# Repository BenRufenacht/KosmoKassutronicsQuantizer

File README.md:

# KosmoKassutronicsQuantizer
 Kassutronics Quantizer in Kosmo Format

[Build Docs from Kassutronics](https://github.com/kassu/kassutronics/blob/master/documentation/Quantizer/Quantizer_Build_Docs_1.1A.pdf)

Status:   
Oct 2023 Updated Back PCB to fix potential shorting issue with the Trigger input jacks and fixed a connection error that prevented free running mode from working. These updates to the back pcb are untested.

License:  
[CC-BY-SA](https://creativecommons.org/licenses/by-sa/3.0/)

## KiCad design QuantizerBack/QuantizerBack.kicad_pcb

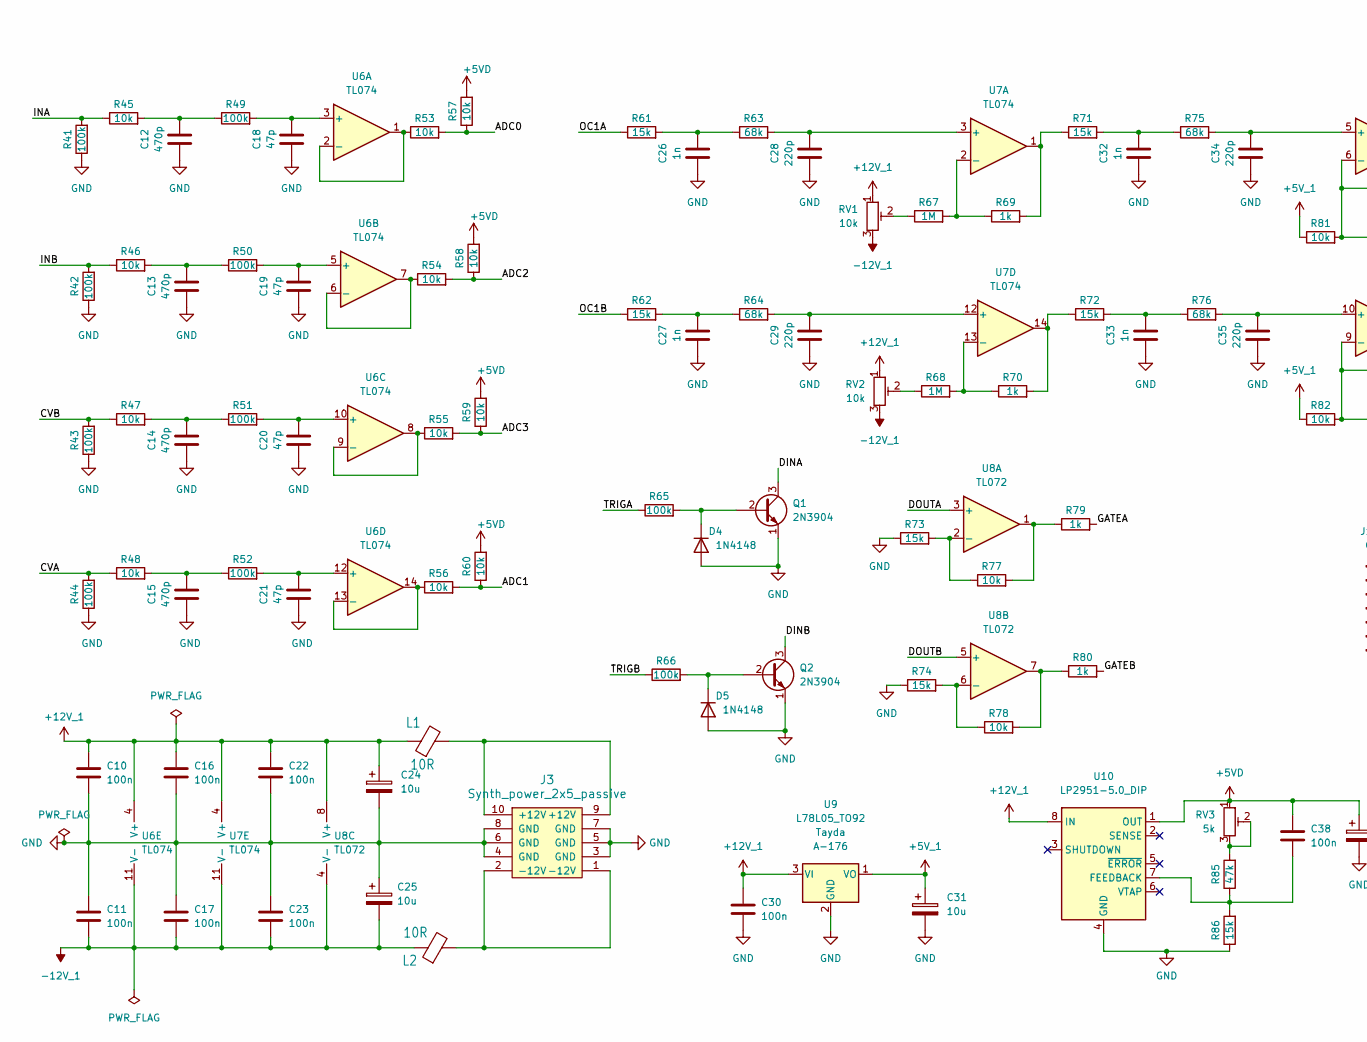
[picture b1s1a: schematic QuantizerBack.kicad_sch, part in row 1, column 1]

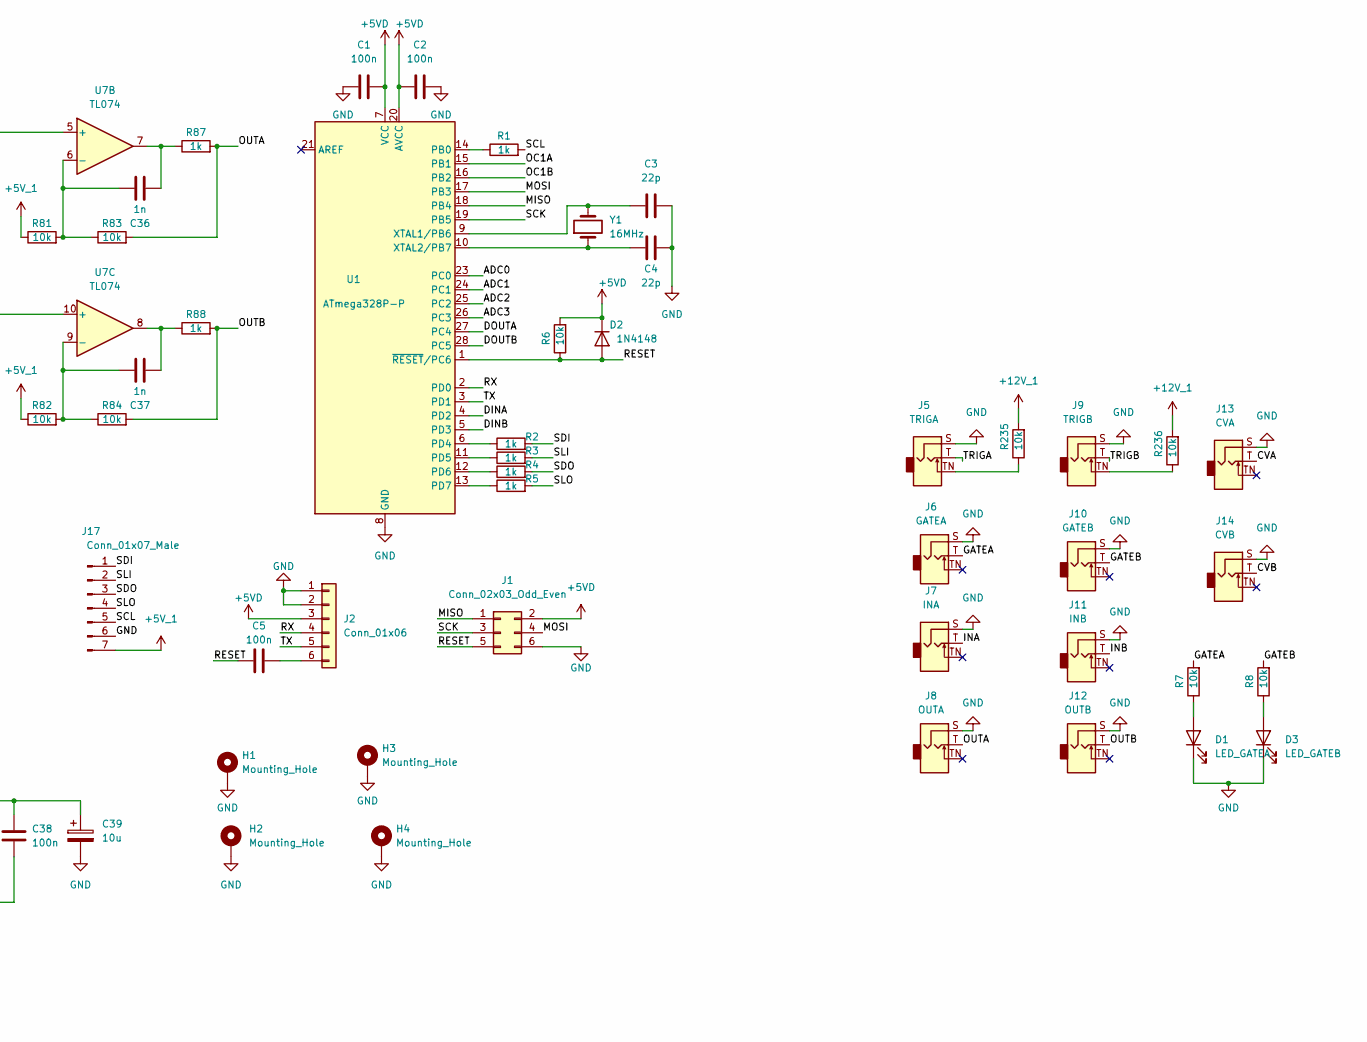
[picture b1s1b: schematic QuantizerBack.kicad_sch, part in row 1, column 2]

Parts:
C1, C2, C5, C10, C11, C16, C17, C22, C23, C30, C38: 100n; C_Rect_L7.2mm_W2.5mm_P5.00mm_FKS2_FKP2_MKS2_MKP2
C3, C4: 22p; C_Rect_L7.2mm_W2.5mm_P5.00mm_FKS2_FKP2_MKS2_MKP2
C12, C13, C14, C15: 470p; C_Rect_L7.2mm_W2.5mm_P5.00mm_FKS2_FKP2_MKS2_MKP2
C18, C19, C20, C21: 47p; C_Rect_L7.2mm_W2.5mm_P5.00mm_FKS2_FKP2_MKS2_MKP2
C24, C25, C31, C39: 10u; CP_Radial_D6.3mm_P2.50mm
C26, C27, C32, C33, C36, C37: 1n; C_Rect_L7.2mm_W2.5mm_P5.00mm_FKS2_FKP2_MKS2_MKP2
C28, C29, C34, C35: 220p; C_Rect_L7.2mm_W2.5mm_P5.00mm_FKS2_FKP2_MKS2_MKP2
D1: LED_GATEA; LED_D5.0mm
D2, D4, D5: 1N4148; D_DO-35_SOD27_P7.62mm_Horizontal
D3: LED_GATEB; LED_D5.0mm
H1, H2, H3, H4: Mounting_Hole; Kosmo_Panel_Mounting_Hole
J1: Conn_02x03_Odd_Even; PinHeader_2x03_P2.54mm_Vertical
J2: Conn_01x06; PinHeader_1x06_P2.54mm_Vertical
J3: Synth_power_2x5_passive; Power_Header
J5: TRIGA; Jack_6.35mm_PJ_629HAN
J6: GATEA; Jack_6.35mm_PJ_629HAN
J7: INA; Jack_6.35mm_PJ_629HAN
J8: OUTA; Jack_6.35mm_PJ_629HAN
J9: TRIGB; Jack_6.35mm_PJ_629HAN
J10: GATEB; Jack_6.35mm_PJ_629HAN
J11: INB; Jack_6.35mm_PJ_629HAN
J12: OUTB; Jack_6.35mm_PJ_629HAN
J13: CVA; Jack_6.35mm_PJ_629HAN
J14: CVB; Jack_6.35mm_PJ_629HAN
J17: Conn_01x07_Male; PinHeader_1x07_P2.54mm_Vertical
L1, L2: 10R; L_Axial_L5.0mm_D3.6mm_P10.00mm_Horizontal_Murata_BL01RN1A2A2
Q1, Q2: 2N3904; TO-92_Inline_Wide
R1, R2, R3, R4, R5, R69, R70, R79, R80, R87, R88: 1k; R_Axial_DIN0207_L6.3mm_D2.5mm_P10.16mm_Horizontal
R6, R7, R8, R45, R46, R47, R48, R53, R54, R55, R56, R57, R58, R59, R60, R77, R78, R81, R82, R83, R84, R235, R236: 10k; R_Axial_DIN0207_L6.3mm_D2.5mm_P10.16mm_Horizontal
R41, R42, R43, R44, R49, R50, R51, R52, R65, R66: 100k; R_Axial_DIN0207_L6.3mm_D2.5mm_P10.16mm_Horizontal
R61, R62, R71, R72, R73, R74, R86: 15k; R_Axial_DIN0207_L6.3mm_D2.5mm_P10.16mm_Horizontal
R63, R64, R75, R76: 68k; R_Axial_DIN0207_L6.3mm_D2.5mm_P10.16mm_Horizontal
R67, R68: 1M; R_Axial_DIN0207_L6.3mm_D2.5mm_P10.16mm_Horizontal
R85: 47k; R_Axial_DIN0207_L6.3mm_D2.5mm_P10.16mm_Horizontal
RV1, RV2: 10k; Potentiometer_Bourns_3296W_Vertical_standard
RV3: 5k; Potentiometer_Bourns_3296W_Vertical_standard
U1: ATmega328P-P; DIP-28_W7.62mm
U6, U7: TL074; DIP-14_W7.62mm_Socket_LongPads
U8: TL072; DIP-8_W7.62mm_Socket_LongPads
U9: L78L05_TO92; TO-92_Inline
U10: LP2951-5.0_DIP; DIP-8_W7.62mm
Y1: 16MHz; Crystal_HC49-U_Vertical

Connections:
+5VD: C1.2, C2.1, C38.1, C39.1, D2.1 (K), J1.2, J2.3, R6.2, R57.2, R58.2, R59.2, R60.2, RV3.1, U1.7 (VCC), U1.20 (AVCC), U10.1 (OUT)
+5V_1: C31.1, J17.7, R81.1, R82.1, U9.1 (VO)
+12V_1: C10.1, C16.1, C22.1, C24.1, C30.1, L1.1, R235.2, R236.2, RV1.1, RV2.1, U6.4 (V+), U7.4 (V+), U8.8 (V+), U9.3 (VI), U10.8 (IN)
-12V_1: C11.1, C17.1, C23.1, C25.2, L2.1, RV1.3, RV2.3, U6.11 (V-), U7.11 (V-), U8.4 (V-)
/ADC0: R53.2, R57.1, U1.23 (PC0)
/ADC1: R56.2, R60.1, U1.24 (PC1)
/ADC2: R54.2, R58.1, U1.25 (PC2)
/ADC3: R55.2, R59.1, U1.26 (PC3)
/CVA: J13.T, R44.2, R48.1
/CVB: J14.T, R43.2, R47.1
/DINA: Q1.3 (C), U1.4 (PD2)
/DINB: Q2.3 (C), U1.5 (PD3)
/DOUTA: U1.27 (PC4), U8.3 (+)
/DOUTB: U1.28 (PC5), U8.5 (+)
/GATEA: J6.T, R7.2, R79.2
/GATEB: J10.T, R8.2, R80.2
/INA: J7.T, R41.2, R45.1
/INB: J11.T, R42.2, R46.1
/MISO: J1.1, U1.18 (PB4)
/MOSI: J1.4, U1.17 (PB3)
/OC1A: R61.1, U1.15 (PB1)
/OC1B: R62.1, U1.16 (PB2)
/OUTA: J8.T, R83.2, R87.2
/OUTB: J12.T, R84.2, R88.2
/RESET: C5.1, D2.2 (A), J1.5, R6.1, U1.1 (~RESET/PC6)
/RX: J2.4, U1.2 (PD0)
/SCK: J1.3, U1.19 (PB5)
/SCL: J17.5, R1.2
/SDI: J17.1, R2.2
/SDO: J17.3, R4.2
/SLI: J17.2, R3.2
/SLO: J17.4, R5.2
/TRIGA: J5.T, R65.1
/TRIGB: J9.T, R66.1
/TX: J2.5, U1.3 (PD1)
GND: C1.1, C2.2, C3.2, C4.2, C10.2, C11.2, C12.1, C13.1, C14.1, C15.1, C16.2, C17.2, C18.1, C19.1, C20.1, C21.1, C22.2, C23.2, C24.2, C25.1, C26.1, C27.1, C28.1, C29.1, C30.2, C31.2, C32.1, C33.1, C34.1, C35.1, C39.2, D1.1 (K), D3.1 (K), D4.2 (A), D5.2 (A), H1.1, H2.1, H3.1, H4.1, J1.6, J2.1, J2.2, J3.3 (GND), J3.4 (GND), J3.5 (GND), J3.6 (GND), J3.7 (GND), J3.8 (GND), J5.S, J6.S, J7.S, J8.S, J9.S, J10.S, J11.S, J12.S, J13.S, J14.S, J17.6, Q1.1 (E), Q2.1 (E), R41.1, R42.1, R43.1, R44.1, R73.1, R74.1, R86.1, U1.8 (GND), U1.22 (GND), U9.2 (GND), U10.4 (GND)
unnamed: C12.2, R45.2, R49.1
unnamed: C13.2, R46.2, R50.1
unnamed: C14.2, R47.2, R51.1
unnamed: C15.2, R48.2, R52.1
unnamed: C26.2, R61.2, R63.1
unnamed: C27.2, R62.2, R64.1
unnamed: C32.2, R71.2, R75.1
unnamed: C33.2, R72.2, R76.1
unnamed: C36.1, R87.1, U7.7
unnamed: C37.1, R88.1, U7.8
unnamed: D1.2 (A), R7.1
unnamed: D3.2 (A), R8.1
unnamed: D4.1 (K), Q1.2 (B), R65.2
unnamed: D5.1 (K), Q2.2 (B), R66.2
unnamed: C5.2, J2.6
unnamed: J3.9 (+12V), J3.10 (+12V), L1.2
unnamed: J3.1 (-12V), J3.2 (-12V), L2.2
unnamed: J5.TN, R235.1
unnamed: J9.TN, R236.1
unnamed: R67.1, RV1.2
unnamed: R68.1, RV2.2
unnamed: R69.2, R71.1, U7.1
unnamed: R70.2, R72.1, U7.14
unnamed: R77.2, R79.1, U8.1
unnamed: R78.2, R80.1, U8.7
unnamed: R85.2, RV3.2, RV3.3
unnamed: R1.1, U1.14 (PB0)
unnamed: R2.1, U1.6 (PD4)
unnamed: R3.1, U1.11 (PD5)
unnamed: R4.1, U1.12 (PD6)
unnamed: R5.1, U1.13 (PD7)
unnamed: C3.1, U1.9 (XTAL1/PB6), Y1.2
unnamed: C4.1, U1.10 (XTAL2/PB7), Y1.1
unnamed: C18.2, R49.2, U6.3 (+)
unnamed: R53.1, U6.1, U6.2 (-)
unnamed: C19.2, R50.2, U6.5 (+)
unnamed: R54.1, U6.6 (-), U6.7
unnamed: C20.2, R51.2, U6.10 (+)
unnamed: R55.1, U6.8, U6.9 (-)
unnamed: C21.2, R52.2, U6.12 (+)
unnamed: R56.1, U6.13 (-), U6.14
unnamed: C28.2, R63.2, U7.3 (+)
unnamed: R67.2, R69.1, U7.2 (-)
unnamed: C34.2, R75.2, U7.5 (+)
unnamed: C36.2, R81.2, R83.1, U7.6 (-)
unnamed: C35.2, R76.2, U7.10 (+)
unnamed: C37.2, R82.2, R84.1, U7.9 (-)
unnamed: C29.2, R64.2, U7.12 (+)
unnamed: R68.2, R70.1, U7.13 (-)
unnamed: R73.2, R77.1, U8.2 (-)
unnamed: R74.2, R78.1, U8.6 (-)
unnamed: C38.2, R85.1, R86.2, U10.7 (FEEDBACK)

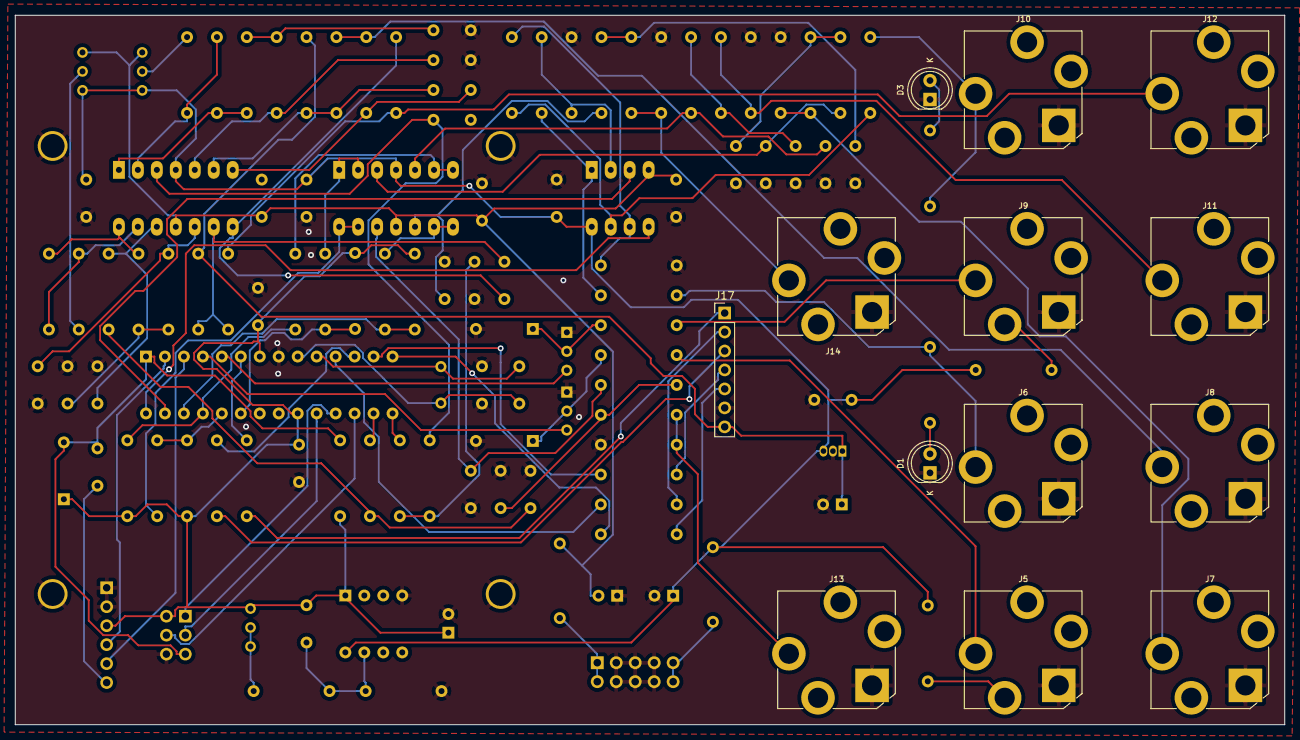
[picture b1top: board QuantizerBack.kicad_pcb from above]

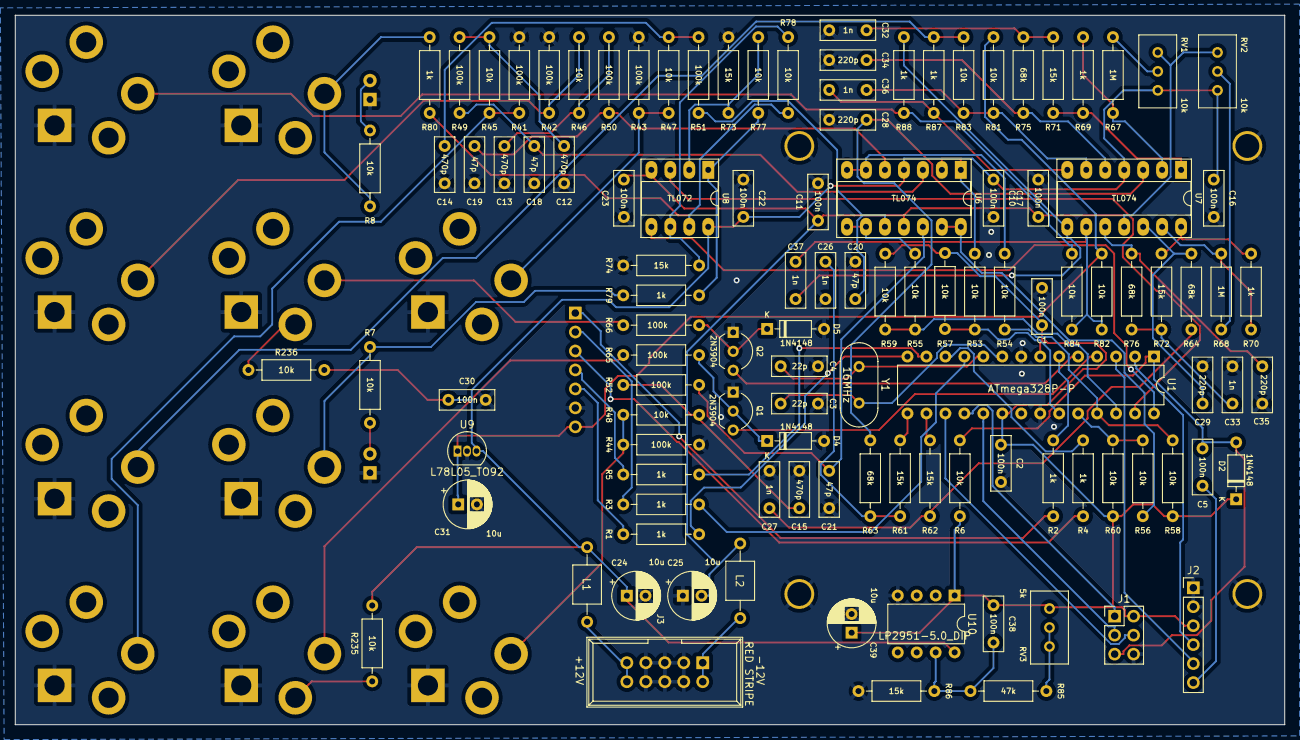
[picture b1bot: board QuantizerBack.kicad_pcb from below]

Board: 2 copper layers, 170.0 x 95.0 mm, 130 parts (113 on the bottom side), 88 nets.

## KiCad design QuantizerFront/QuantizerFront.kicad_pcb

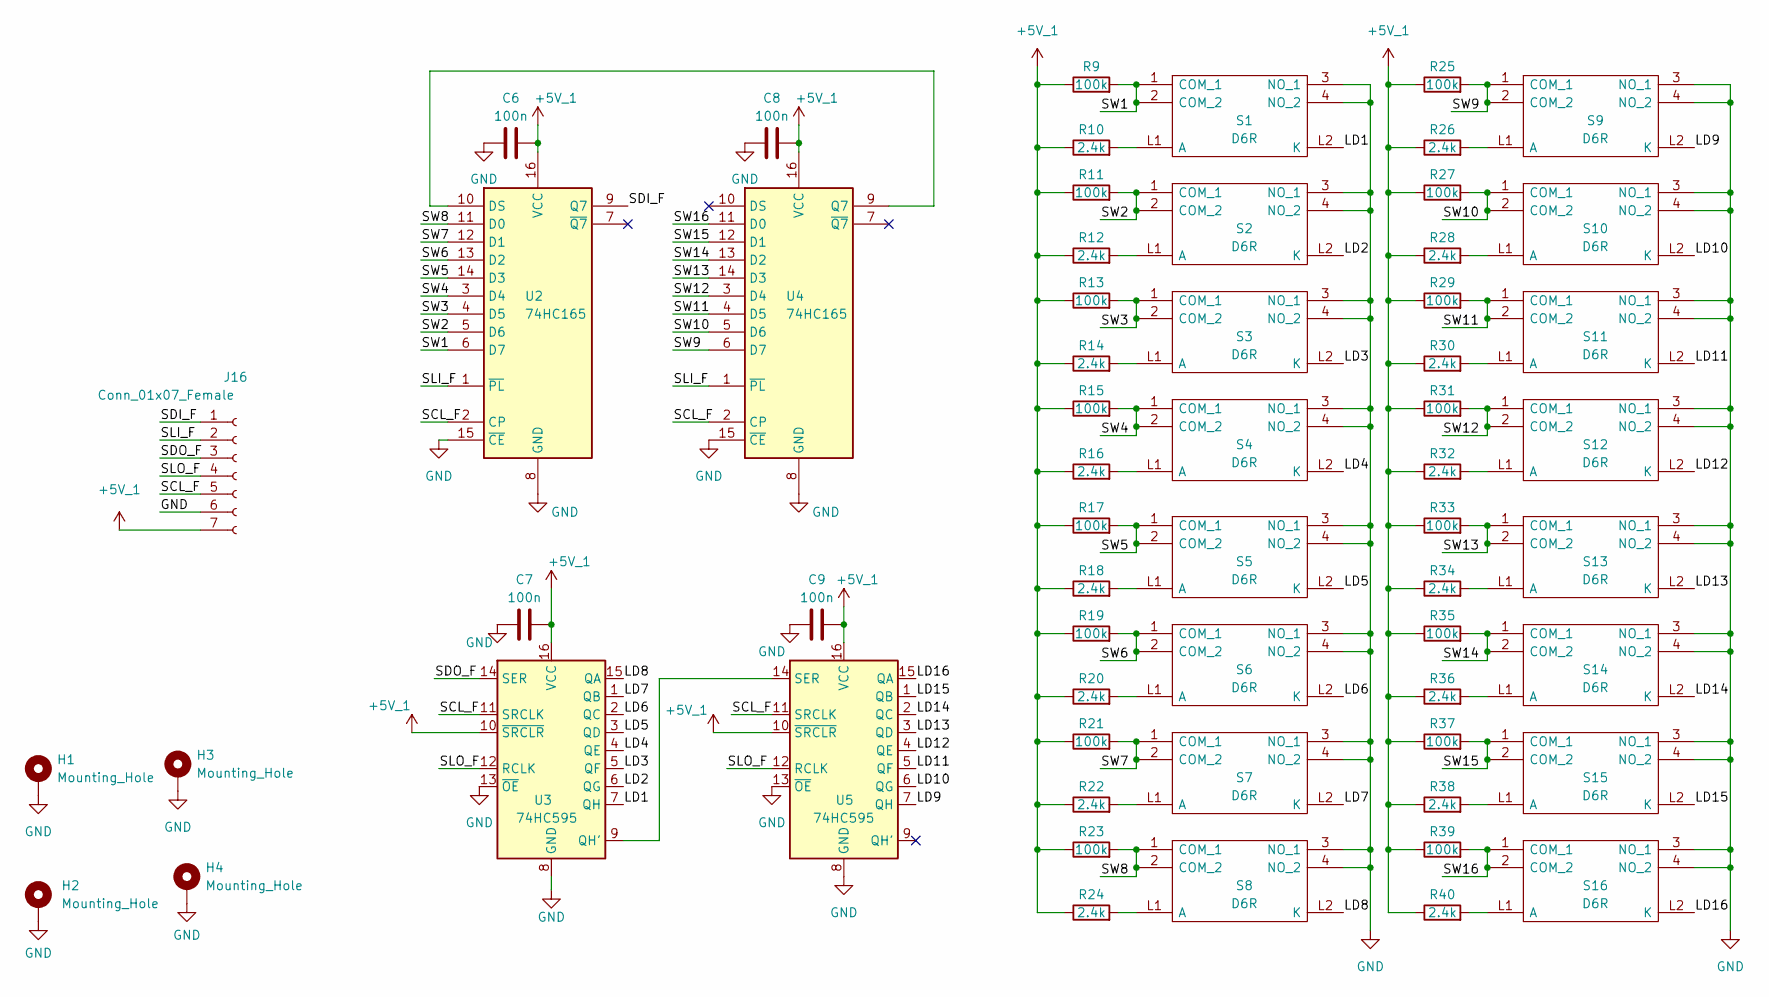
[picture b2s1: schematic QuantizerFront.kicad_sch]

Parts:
C6, C7, C8, C9: 100n; C_Rect_L7.2mm_W2.5mm_P5.00mm_FKS2_FKP2_MKS2_MKP2
H1, H2, H3, H4: Mounting_Hole; Kosmo_Panel_Mounting_Hole
J16: Conn_01x07_Female; PinSocket_1x07_P2.54mm_Vertical
R9, R11, R13, R15, R17, R19, R21, R23, R25, R27, R29, R31, R33, R35, R37, R39: 100k; R_Axial_DIN0207_L6.3mm_D2.5mm_P10.16mm_Horizontal
R10, R12, R14, R16, R18, R20, R22, R24, R26, R28, R30, R32, R34, R36, R38, R40: 2.4k; R_Axial_DIN0207_L6.3mm_D2.5mm_P10.16mm_Horizontal
S1, S2, S3, S4, S5, S6, S7, S8, S9, S10, S11, S12, S13, S14, S15, S16: D6R; Manufacturer_Part_Number D6RLGNF1+LFS
U2, U4: 74HC165; DIP-16_W7.62mm_Socket_LongPads
U3, U5: 74HC595; DIP-16_W7.62mm_Socket_LongPads

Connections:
+5V_1: C6.2, C7.2, C8.2, C9.2, J16.7, R9.1, R10.1, R11.1, R12.1, R13.1, R14.1, R15.1, R16.1, R17.1, R18.1, R19.1, R20.1, R21.1, R22.1, R23.1, R24.1, R25.1, R26.1, R27.1, R28.1, R29.1, R30.1, R31.1, R32.1, R33.1, R34.1, R35.1, R36.1, R37.1, R38.1, R39.1, R40.1, U2.16 (VCC), U3.10 (~SRCLR), U3.16 (VCC), U4.16 (VCC), U5.10 (~SRCLR), U5.16 (VCC)
/LD1: S1.L2 (K), U3.7 (QH)
/LD2: S2.L2 (K), U3.6 (QG)
/LD3: S3.L2 (K), U3.5 (QF)
/LD4: S4.L2 (K), U3.4 (QE)
/LD5: S5.L2 (K), U3.3 (QD)
/LD6: S6.L2 (K), U3.2 (QC)
/LD7: S7.L2 (K), U3.1 (QB)
/LD8: S8.L2 (K), U3.15 (QA)
/LD9: S9.L2 (K), U5.7 (QH)
/LD10: S10.L2 (K), U5.6 (QG)
/LD11: S11.L2 (K), U5.5 (QF)
/LD12: S12.L2 (K), U5.4 (QE)
/LD13: S13.L2 (K), U5.3 (QD)
/LD14: S14.L2 (K), U5.2 (QC)
/LD15: S15.L2 (K), U5.1 (QB)
/LD16: S16.L2 (K), U5.15 (QA)
/SCL_F: J16.5, U2.2 (CP), U3.11 (SRCLK), U4.2 (CP), U5.11 (SRCLK)
/SDI_F: J16.1, U2.9 (Q7)
/SDO_F: J16.3, U3.14 (SER)
/SLI_F: J16.2, U2.1 (~PL), U4.1 (~PL)
/SLO_F: J16.4, U3.12 (RCLK), U5.12 (RCLK)
/SW1: R9.2, S1.1 (COM_1), S1.2 (COM_2), U2.6 (D7)
/SW2: R11.2, S2.1 (COM_1), S2.2 (COM_2), U2.5 (D6)
/SW3: R13.2, S3.1 (COM_1), S3.2 (COM_2), U2.4 (D5)
/SW4: R15.2, S4.1 (COM_1), S4.2 (COM_2), U2.3 (D4)
/SW5: R17.2, S5.1 (COM_1), S5.2 (COM_2), U2.14 (D3)
/SW6: R19.2, S6.1 (COM_1), S6.2 (COM_2), U2.13 (D2)
/SW7: R21.2, S7.1 (COM_1), S7.2 (COM_2), U2.12 (D1)
/SW8: R23.2, S8.1 (COM_1), S8.2 (COM_2), U2.11 (D0)
/SW9: R25.2, S9.1 (COM_1), S9.2 (COM_2), U4.6 (D7)
/SW10: R27.2, S10.1 (COM_1), S10.2 (COM_2), U4.5 (D6)
/SW11: R29.2, S11.1 (COM_1), S11.2 (COM_2), U4.4 (D5)
/SW12: R31.2, S12.1 (COM_1), S12.2 (COM_2), U4.3 (D4)
/SW13: R33.2, S13.1 (COM_1), S13.2 (COM_2), U4.14 (D3)
/SW14: R35.2, S14.1 (COM_1), S14.2 (COM_2), U4.13 (D2)
/SW15: R37.2, S15.1 (COM_1), S15.2 (COM_2), U4.12 (D1)
/SW16: R39.2, S16.1 (COM_1), S16.2 (COM_2), U4.11 (D0)
GND: C6.1, C7.1, C8.1, C9.1, H1.1, H2.1, H3.1, H4.1, J16.6, S1.3 (NO_1), S1.4 (NO_2), S2.3 (NO_1), S2.4 (NO_2), S3.3 (NO_1), S3.4 (NO_2), S4.3 (NO_1), S4.4 (NO_2), S5.3 (NO_1), S5.4 (NO_2), S6.3 (NO_1), S6.4 (NO_2), S7.3 (NO_1), S7.4 (NO_2), S8.3 (NO_1), S8.4 (NO_2), S9.3 (NO_1), S9.4 (NO_2), S10.3 (NO_1), S10.4 (NO_2), S11.3 (NO_1), S11.4 (NO_2), S12.3 (NO_1), S12.4 (NO_2), S13.3 (NO_1), S13.4 (NO_2), S14.3 (NO_1), S14.4 (NO_2), S15.3 (NO_1), S15.4 (NO_2), S16.3 (NO_1), S16.4 (NO_2), U2.8 (GND), U2.15 (~CE), U3.8 (GND), U3.13 (~OE), U4.8 (GND), U4.15 (~CE), U5.8 (GND), U5.13 (~OE)
unnamed: R10.2, S1.L1 (A)
unnamed: R12.2, S2.L1 (A)
unnamed: R14.2, S3.L1 (A)
unnamed: R16.2, S4.L1 (A)
unnamed: R18.2, S5.L1 (A)
unnamed: R20.2, S6.L1 (A)
unnamed: R22.2, S7.L1 (A)
unnamed: R24.2, S8.L1 (A)
unnamed: R26.2, S9.L1 (A)
unnamed: R28.2, S10.L1 (A)
unnamed: R30.2, S11.L1 (A)
unnamed: R32.2, S12.L1 (A)
unnamed: R34.2, S13.L1 (A)
unnamed: R36.2, S14.L1 (A)
unnamed: R38.2, S15.L1 (A)
unnamed: R40.2, S16.L1 (A)
unnamed: U2.10 (DS), U4.9 (Q7)
unnamed: U3.9 (QH'), U5.14 (SER)

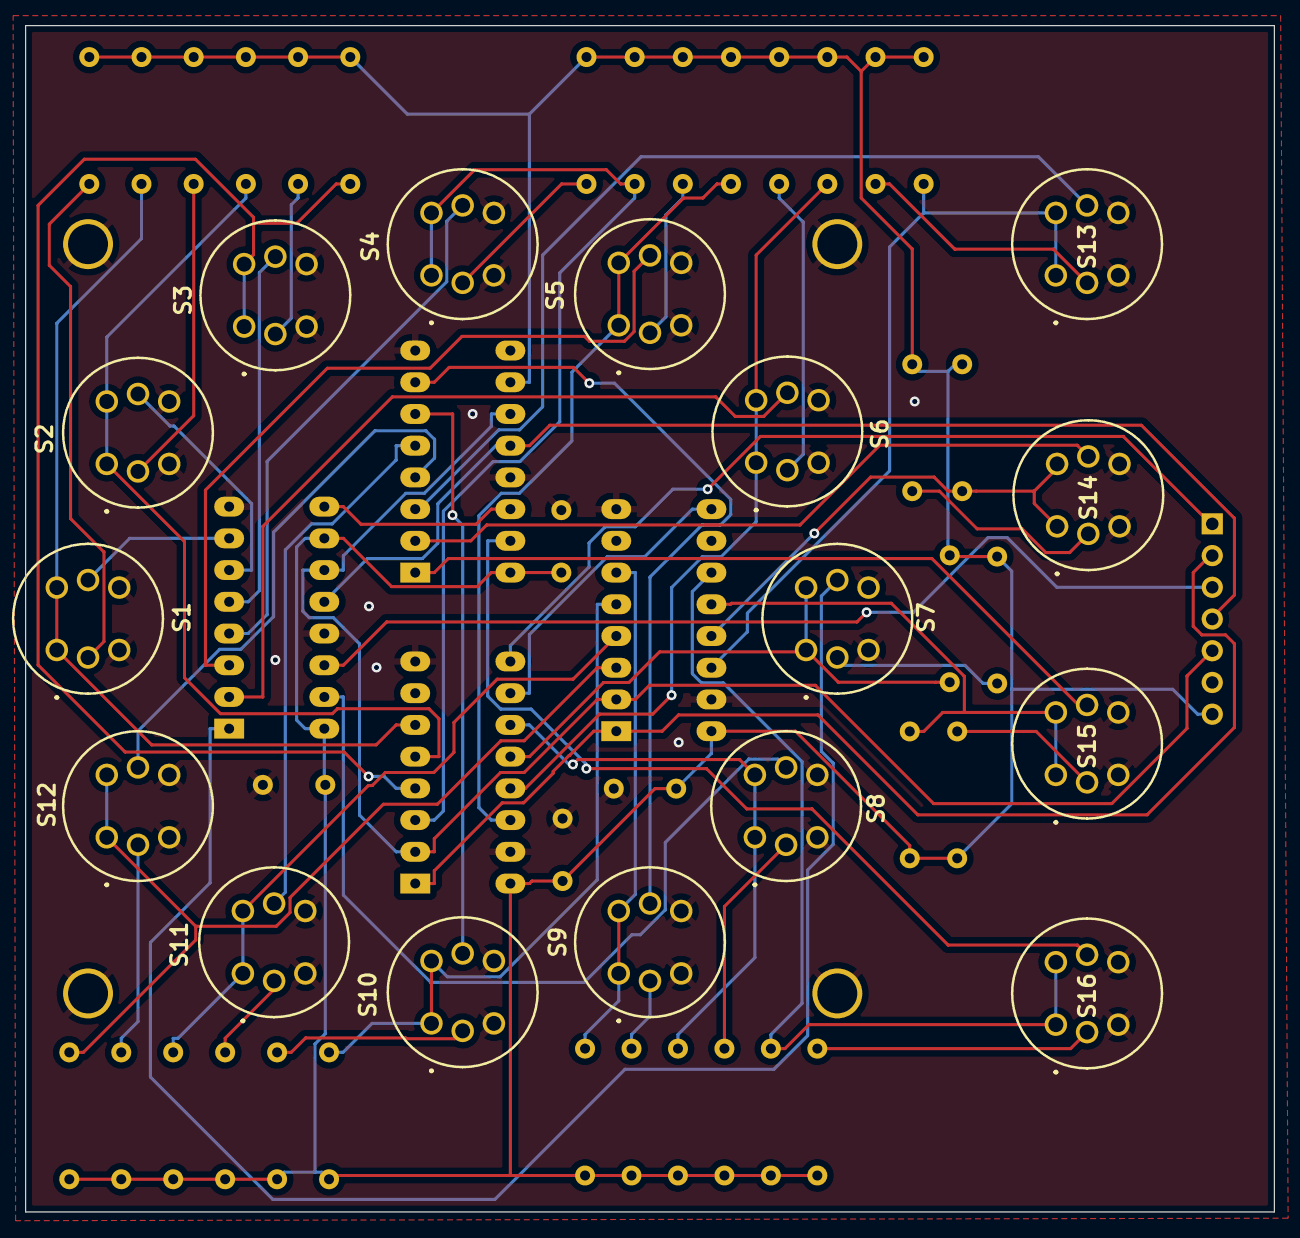
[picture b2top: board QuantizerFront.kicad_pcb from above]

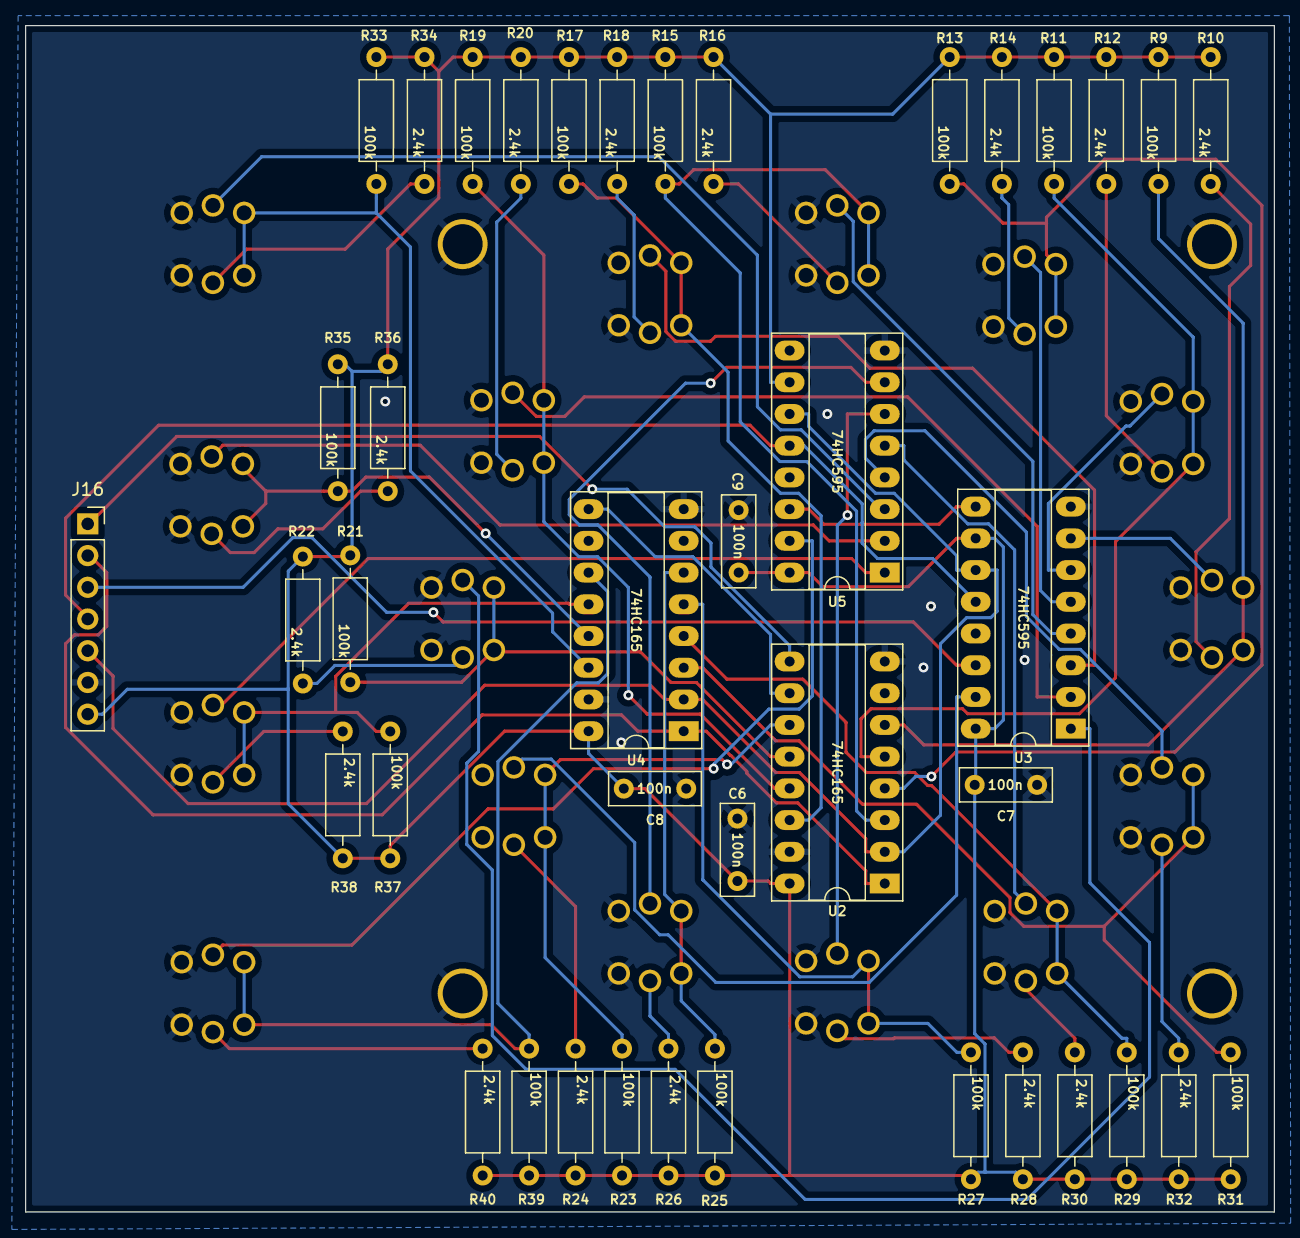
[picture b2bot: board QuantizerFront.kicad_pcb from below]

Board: 2 copper layers, 100.0 x 95.0 mm, 61 parts (41 on the bottom side), 57 nets.

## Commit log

2022-07-13 Change graphic name
2022-07-13 Updated Graphics
2022-07-14 Manufacturing Updates
2022-07-14 Gerber Updates
2023-03-18 Update after testing
    Module is fully tested and working
2023-10-14 Fix Trigger Input Jack Issue
    Previous version of these boards did not have the tip normal of the input jacks connected to +12v to allow free running mode. Kassutronics updated the documentation to add a resistor that prevents sh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
2023-10-14 Update readme
    Update readme to note that the pcb is untested.
